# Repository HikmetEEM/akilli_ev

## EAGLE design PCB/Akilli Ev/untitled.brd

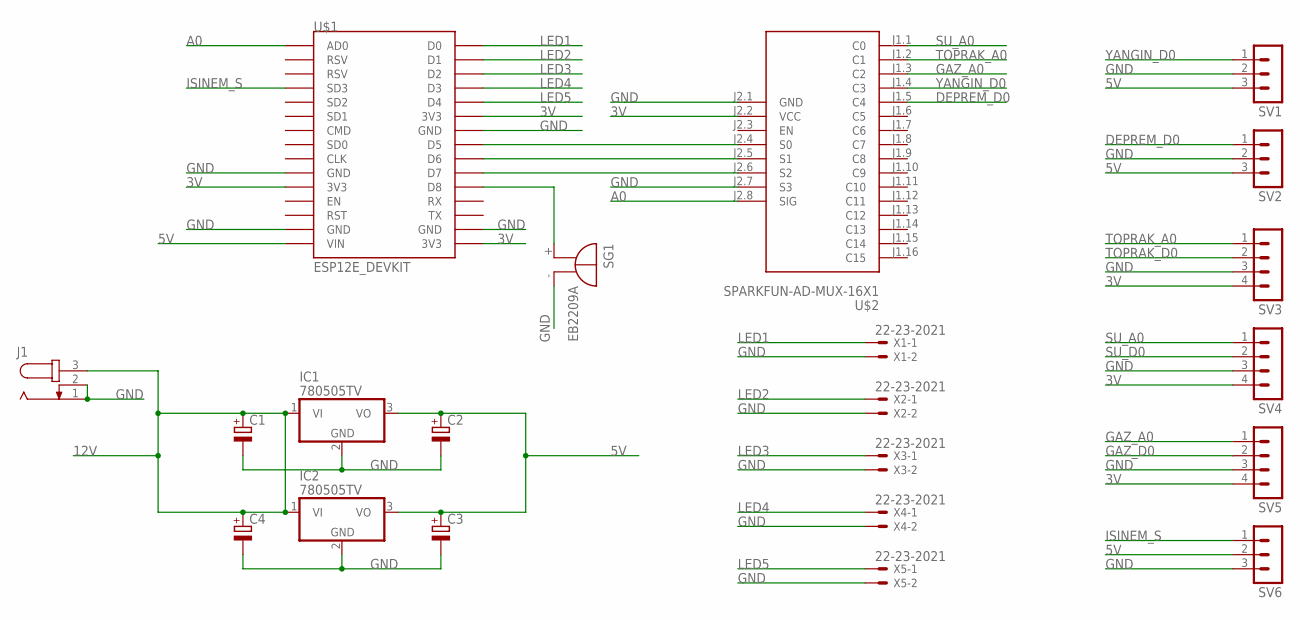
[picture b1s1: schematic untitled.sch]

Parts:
C1, C2, C3, C4: CPOL-EUE5-5; E5-5
IC1, IC2: 780505TV; TO220V
J1: JACK-PLUG1; SPC4078
SG1: EB2209A
SV1, SV2, SV6: MA03-1
SV3, SV4, SV5: MA04-1
U$1: ESP12E_DEVKIT
U$2: SPARKFUN-AD-MUX-16X1
X1, X2, X3, X4, X5: 22-23-2021

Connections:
3V: SV3.4, SV4.4, SV5.4, U$1.3V3@0 (3V3), U$1.3V3@1 (3V3), U$1.3V3@2 (3V3), U$2.J2.2 (VCC)
5V: C2.+, C3.+, IC1.3 (VO), IC2.3 (VO), SV1.3, SV2.3, SV6.2, U$1.VIN
12V: C1.+, C4.+, IC1.1 (VI), IC2.1 (VI), J1.3
A0: U$1.AD0, U$2.J2.8 (SIG)
DEPREM_D0: SV2.1, U$2.J1.5 (C4)
GAZ_A0: SV5.1, U$2.J1.3 (C2)
GAZ_D0: SV5.2
GND: C1.-, C2.-, C3.-, C4.-, IC1.2 (GND), IC2.2 (GND), J1.1, J1.2, SG1.-, SV1.2, SV2.2, SV3.3, SV4.3, SV5.3, SV6.3, U$1.GND@0 (GND), U$1.GND@1 (GND), U$1.GND@2 (GND), U$1.GND@3 (GND), U$2.J2.1 (GND), U$2.J2.7 (S3), X1.2, X2.2, X3.2, X4.2, X5.2
ISINEM_S: SV6.1, U$1.SD3
LED1: U$1.D0, X1.1
LED2: U$1.D1, X2.1
LED3: U$1.D2, X3.1
LED4: U$1.D3, X4.1
LED5: U$1.D4, X5.1
unnamed: U$1.D5, U$2.J2.4 (S0)
unnamed: U$1.D6, U$2.J2.5 (S1)
unnamed: U$1.D7, U$2.J2.6 (S2)
unnamed: SG1.+, U$1.D8
SU_A0: SV4.1, U$2.J1.1 (C0)
SU_D0: SV4.2
TOPRAK_A0: SV3.1, U$2.J1.2 (C1)
TOPRAK_D0: SV3.2
YANGIN_D0: SV1.1, U$2.J1.4 (C3)

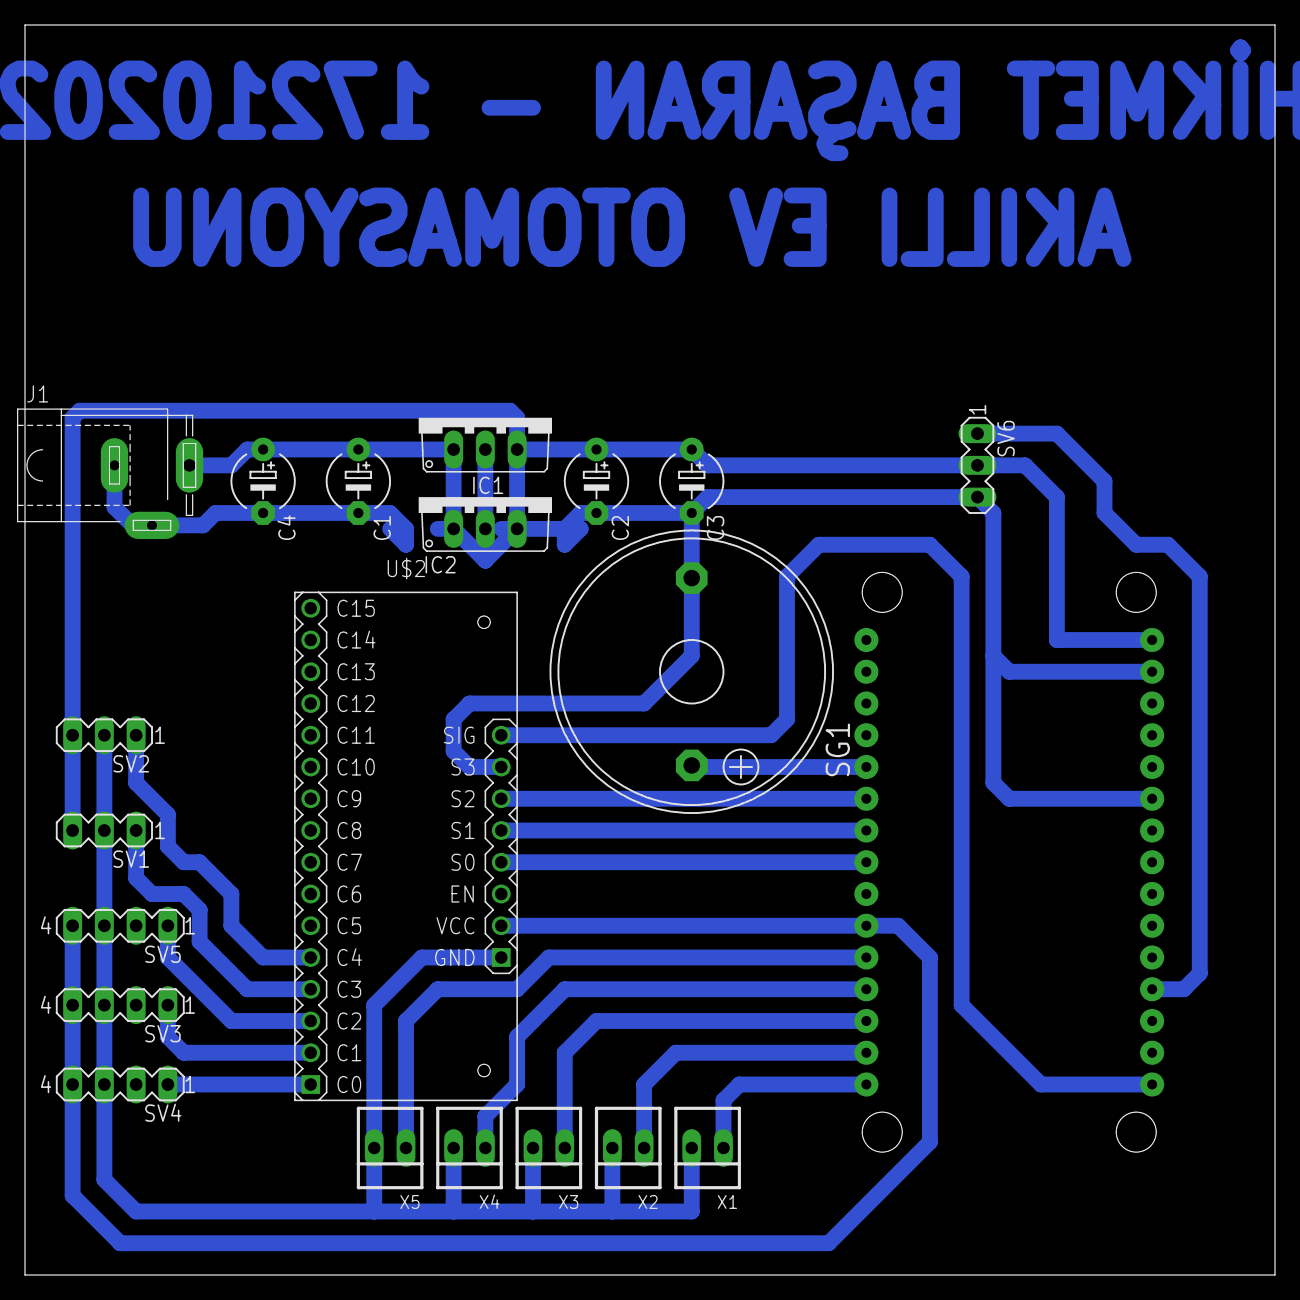
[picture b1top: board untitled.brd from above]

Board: 2 copper layers, 100.0 x 100.0 mm, 21 parts (0 on the bottom side), 20 nets.

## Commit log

2021-03-29 1.gün
    mazlemerin sağlamlıkları yapıldı gerekli örnejler bulundu alev ve ısınem eskik
2021-03-31 anakod
    anakod yapıyoruz
2021-04-02 PCB added.
2021-05-10 yenilendi

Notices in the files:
parts and their libraries:
diy-modules: Released under the Creative Commons Attribution 4.0 International License: http://creativecommons.org/licenses/by/4.0
